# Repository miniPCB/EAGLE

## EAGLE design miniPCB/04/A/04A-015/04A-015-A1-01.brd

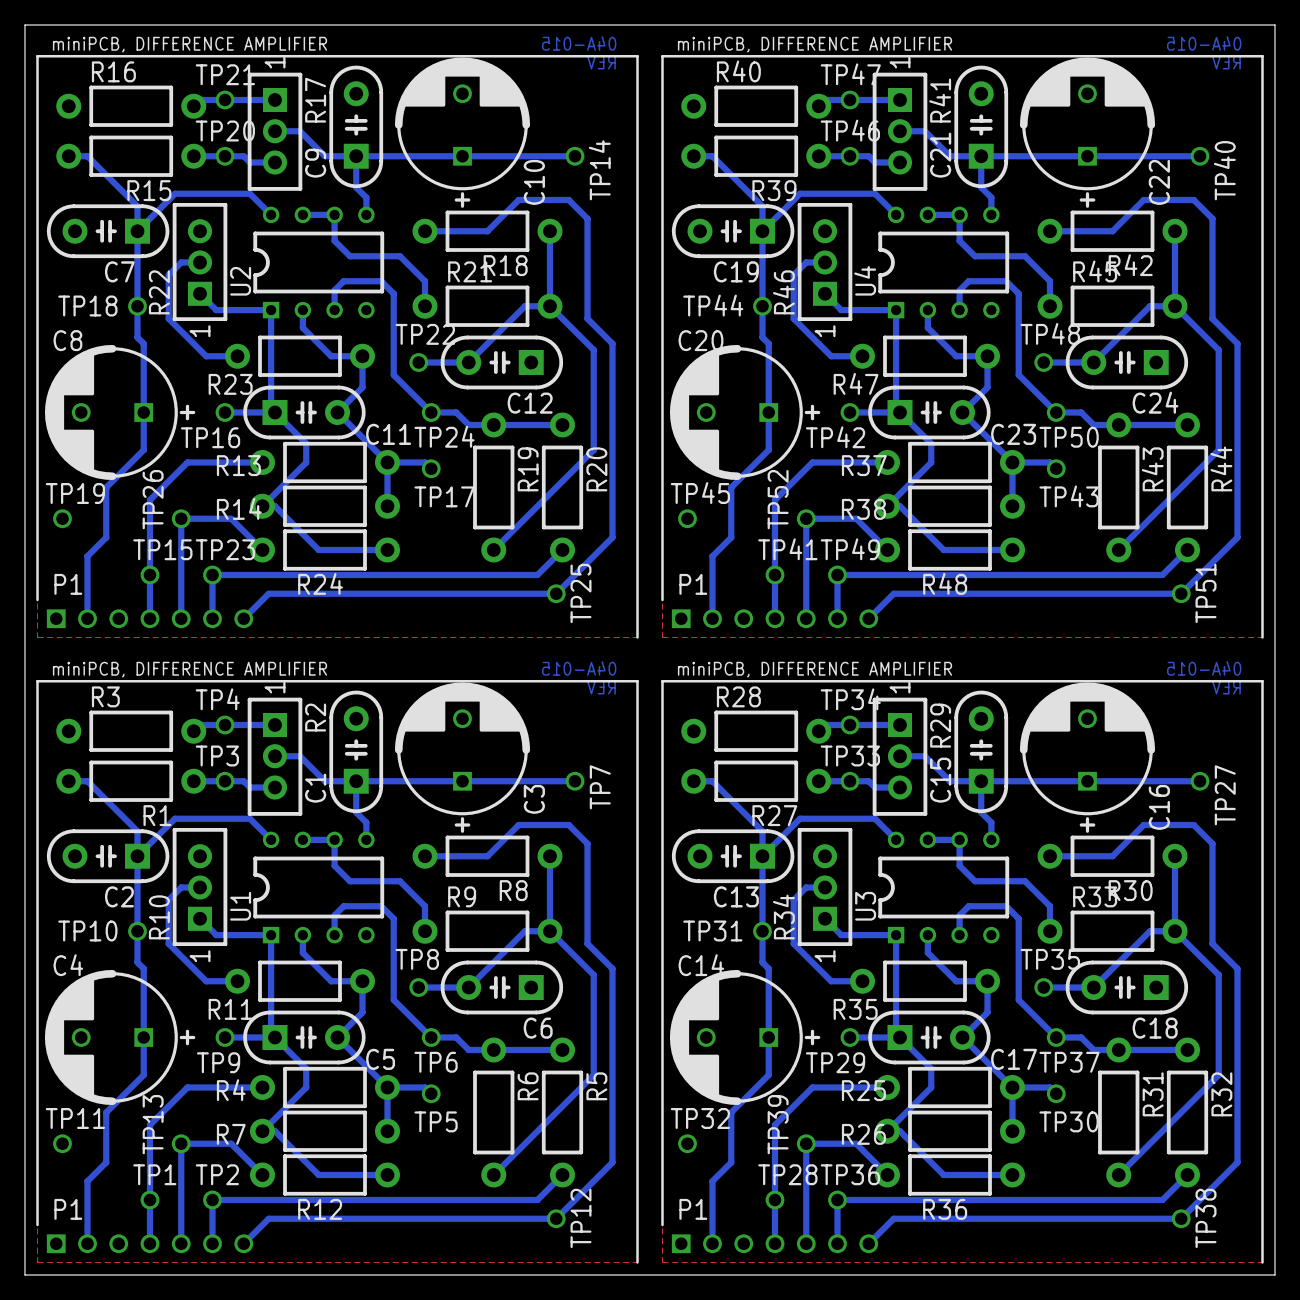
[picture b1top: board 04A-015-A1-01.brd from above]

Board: 2 copper layers, 100.0 x 100.0 mm, 136 parts (0 on the bottom side), 60 nets.

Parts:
C1, C2, C5, C6, C7, C9, C11, C12, C13, C15, C17, C18, C19, C21, C23, C24: C050-024X044
C3, C4, C8, C10, C14, C16, C20, C22: C5MM
P1, P2, P3, P4: PINS_1X7
R1, R3, R4, R5, R6, R7, R8, R9, R11, R12, R13, R14, R15, R16, R18, R19, R20, R21, R23, R24, R25, R26, R27, R28, R30, R31, R32, R33, R35, R36, R37, R38, R39, R40, R42, R43, R44, R45, R47, R48: 0207/10
R2, R10, R17, R22, R29, R34, R41, R46: TRIM_0100
TP1, TP2, TP3, TP4, TP5, TP6, TP7, TP8, TP9, TP10, TP11, TP12, TP13, TP14, TP15, TP16, TP17, TP18, TP19, TP20, TP21, TP22, TP23, TP24, TP25, TP26, TP27, TP28, TP29, TP30, TP31, TP32, TP33, TP34, TP35, TP36, TP37, TP38, TP39, TP40, TP41, TP42, TP43, TP44, TP45, TP46, TP47, TP48, TP49, TP50, TP51, TP52: PINS_1_TESTPOINT_KE5000_NOTEXT
U1, U2, U3, U4: DIL08
U$1, U$2, U$3, U$4: CLASSIC-50; PCB50

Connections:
GND: C1.2, C2.2, C3.-, C4.-, C6.1, P2.1, R3.1, TP11.1, U1.4
GND1: C7.2, C8.-, C9.2, C10.-, C12.1, P1.1, R16.1, TP19.1, U2.4
GND2: C13.2, C14.-, C15.2, C16.-, C18.1, P3.1, R28.1, TP32.1, U3.4
GND3: C19.2, C20.-, C21.2, C22.-, C24.1, P4.1, R40.1, TP45.1, U4.4
IN+: P2.4, R4.2, TP1.1
IN+1: P1.4, R13.2, TP15.1
IN+2: P3.4, R25.2, TP28.1
IN+3: P4.4, R37.2, TP41.1
IN-: P2.6, R5.2, TP2.1
IN-1: P1.6, R20.2, TP23.1
IN-2: P3.6, R32.2, TP36.1
IN-3: P4.6, R44.2, TP49.1
unnamed: R22.2, R23.2
unnamed: R34.2, R35.2
unnamed: R46.2, R47.2
unnamed: R10.2, R11.2
OUT: C5.1, R7.2, R10.1, R12.1, TP9.1, U1.1
OUT1: C11.1, R14.2, R22.1, R24.1, TP16.1, U2.1
OUT2: C17.1, R26.2, R34.1, R36.1, TP29.1, U3.1
OUT3: C23.1, R38.2, R46.1, R48.1, TP42.1, U4.1
OUTPUT: P2.5, R12.2, TP13.1
OUTPUT1: P1.5, R24.2, TP26.1
OUTPUT2: P3.5, R36.2, TP39.1
OUTPUT3: P4.5, R48.2, TP52.1
OUTREF: P2.7, R8.2, TP12.1
OUTREF1: P1.7, R18.2, TP25.1
OUTREF2: P3.7, R30.2, TP38.1
OUTREF3: P4.7, R42.2, TP51.1
P1.1: R2.1, R3.2, TP4.1
P1.2: R15.1, R17.3, TP20.1
P1.3: R1.1, R2.3, TP3.1
P1.4: R16.2, R17.1, TP21.1
P1.5: R27.1, R29.3, TP33.1
P1.6: R28.2, R29.1, TP34.1
P1.7: R39.1, R41.3, TP46.1
P1.8: R40.2, R41.1, TP47.1
REF: C1.1, C3.+, R2.2, TP7.1, U1.5
REF1: C9.1, C10.+, R17.2, TP14.1, U2.5
REF2: C15.1, C16.+, R29.2, TP27.1, U3.5
REF3: C21.1, C22.+, R41.2, TP40.1, U4.5
V+: C2.1, C4.+, P2.2, R1.2, TP10.1, U1.8
V+1: C7.1, C8.+, P1.2, R15.2, TP18.1, U2.8
V+2: C13.1, C14.+, P3.2, R27.2, TP31.1, U3.8
V+3: C19.1, C20.+, P4.2, R39.2, TP44.1, U4.8
VFB: C5.2, R4.1, R7.1, R11.1, TP5.1, U1.2
VFB1: C11.2, R13.1, R14.1, R23.1, TP17.1, U2.2
VFB2: C17.2, R25.1, R26.1, R35.1, TP30.1, U3.2
VFB3: C23.2, R37.1, R38.1, R47.1, TP43.1, U4.2
VFBREF: R9.1, U1.6, U1.7
VFBREF1: R21.1, U2.6, U2.7
VFBREF2: R33.1, U3.6, U3.7
VFBREF3: R45.1, U4.6, U4.7
VPOS: R5.1, R6.1, TP6.1, U1.3
VPOS1: R19.1, R20.1, TP24.1, U2.3
VPOS2: R31.1, R32.1, TP37.1, U3.3
VPOS3: R43.1, R44.1, TP50.1, U4.3
VREF: C6.2, R6.2, R8.1, R9.2, TP8.1
VREF1: C12.2, R18.1, R19.2, R21.2, TP22.1
VREF2: C18.2, R30.1, R31.2, R33.2, TP35.1
VREF3: C24.2, R42.1, R43.2, R45.2, TP48.1

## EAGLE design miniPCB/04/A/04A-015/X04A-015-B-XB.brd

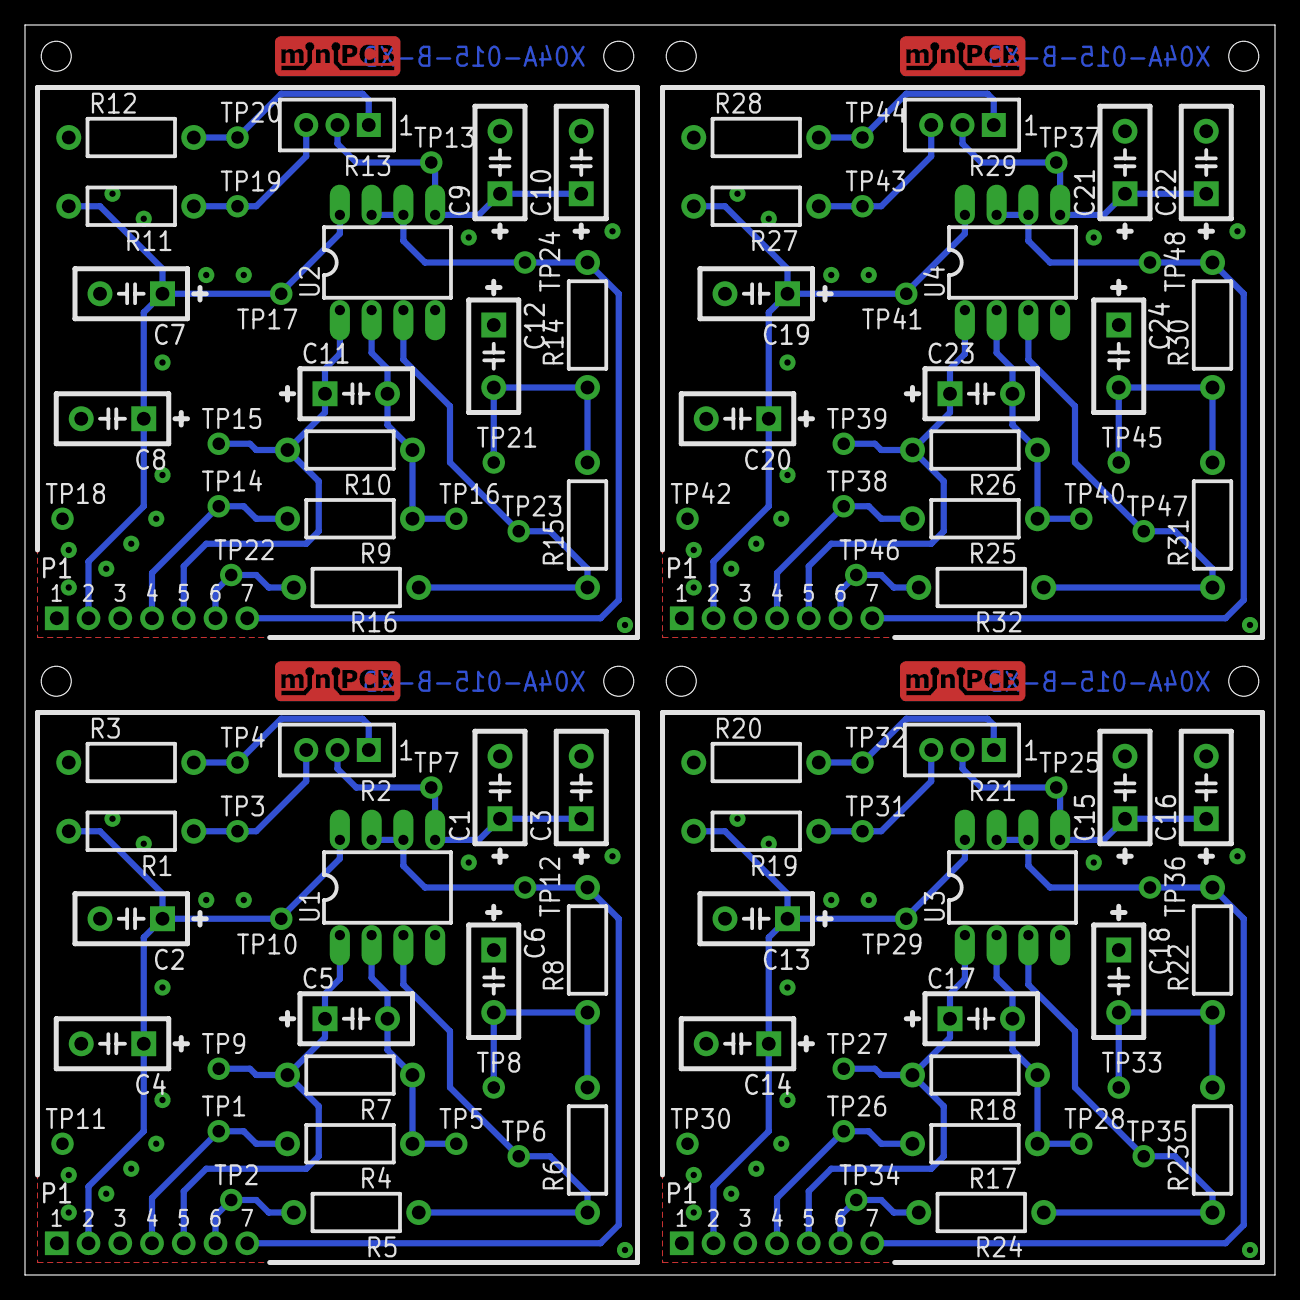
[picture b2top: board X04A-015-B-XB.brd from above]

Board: 2 copper layers, 100.0 x 100.0 mm, 113 parts (0 on the bottom side), 48 nets.

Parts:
C1, C2, C3, C4, C5, C6, C7, C8, C9, C10, C11, C12, C13, C14, C15, C16, C17, C18, C19, C20, C21, C22, C23, C24: C050-024X044
E$1: MINIPCB_PANEL_IMAGEFRAME
P1-, P1-1, P1-2, P1-3: MINIPCB_7P_50X50
R1, R3, R4, R5, R6, R7, R8, R9, R10, R11, R12, R14, R15, R16, R17, R18, R19, R20, R22, R23, R24, R25, R26, R27, R28, R30, R31, R32: 0207/10
R2, R13, R21, R29: TRIM_0100
TP1, TP2, TP3, TP4, TP5, TP6, TP7, TP8, TP9, TP10, TP11, TP12, TP13, TP14, TP15, TP16, TP17, TP18, TP19, TP20, TP21, TP22, TP23, TP24, TP25, TP26, TP27, TP28, TP29, TP30, TP31, TP32, TP33, TP34, TP35, TP36, TP37, TP38, TP39, TP40, TP41, TP42, TP43, TP44, TP45, TP46, TP47, TP48: PINS_1_TESTPOINT_KE5000_NOTEXT
U1, U2, U3, U4: DIL08

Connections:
GND: C1.2, C2.2, C3.2, C4.2, C6.1, P1-.1, R3.1, TP11.1, U1.4
GND1: C7.2, C8.2, C9.2, C10.2, C12.1, P1-1.1, R12.1, TP18.1, U2.4
GND2: C13.2, C14.2, C15.2, C16.2, C18.1, P1-2.1, R20.1, TP30.1, U3.4
GND3: C19.2, C20.2, C21.2, C22.2, C24.1, P1-3.1, R28.1, TP42.1, U4.4
IN: P1-.4, R4.2, TP1.1
IN1: P1-1.4, R9.2, TP14.1
IN2: P1-2.4, R17.2, TP26.1
IN3: P1-3.4, R25.2, TP38.1
unnamed: C1.1, C3.1, R2.2, TP7.1, U1.5
unnamed: C6.2, R6.2, R8.1, TP8.1
unnamed: R5.1, R6.1, TP6.1, U1.3
unnamed: P1-.6, R5.2, TP2.1
unnamed: C9.1, C10.1, R13.2, TP13.1, U2.5
unnamed: C12.2, R14.1, R15.2, TP21.1
unnamed: R15.1, R16.1, TP23.1, U2.3
unnamed: P1-1.6, R16.2, TP22.1
unnamed: C15.1, C16.1, R21.2, TP25.1, U3.5
unnamed: C18.2, R22.1, R23.2, TP33.1
unnamed: R23.1, R24.1, TP35.1, U3.3
unnamed: P1-2.6, R24.2, TP34.1
unnamed: C21.1, C22.1, R29.2, TP37.1, U4.5
unnamed: C24.2, R30.1, R31.2, TP45.1
unnamed: R31.1, R32.1, TP47.1, U4.3
unnamed: P1-3.6, R32.2, TP46.1
OUT: C5.1, P1-.5, R7.2, TP9.1, U1.1
OUT1: C11.1, P1-1.5, R10.2, TP15.1, U2.1
OUT2: C17.1, P1-2.5, R18.2, TP27.1, U3.1
OUT3: C23.1, P1-3.5, R26.2, TP39.1, U4.1
P1.1: R2.1, R3.2, TP4.1
P1.2: R11.1, R13.3, TP19.1
P1.3: R1.1, R2.3, TP3.1
P1.4: R12.2, R13.1, TP20.1
P1.5: R19.1, R21.3, TP31.1
P1.6: R20.2, R21.1, TP32.1
P1.7: R27.1, R29.3, TP43.1
P1.8: R28.2, R29.1, TP44.1
V+: C2.1, C4.1, P1-.2, R1.2, TP10.1, U1.8
V+1: C7.1, C8.1, P1-1.2, R11.2, TP17.1, U2.8
V+2: C13.1, C14.1, P1-2.2, R19.2, TP29.1, U3.8
V+3: C19.1, C20.1, P1-3.2, R27.2, TP41.1, U4.8
VFB: C5.2, R4.1, R7.1, TP5.1, U1.2
VFB1: C11.2, R9.1, R10.1, TP16.1, U2.2
VFB2: C17.2, R17.1, R18.1, TP28.1, U3.2
VFB3: C23.2, R25.1, R26.1, TP40.1, U4.2
VREF: P1-.7, R8.2, TP12.1, U1.6, U1.7
VREF1: P1-1.7, R14.2, TP24.1, U2.6, U2.7
VREF2: P1-2.7, R22.2, TP36.1, U3.6, U3.7
VREF3: P1-3.7, R30.2, TP48.1, U4.6, U4.7

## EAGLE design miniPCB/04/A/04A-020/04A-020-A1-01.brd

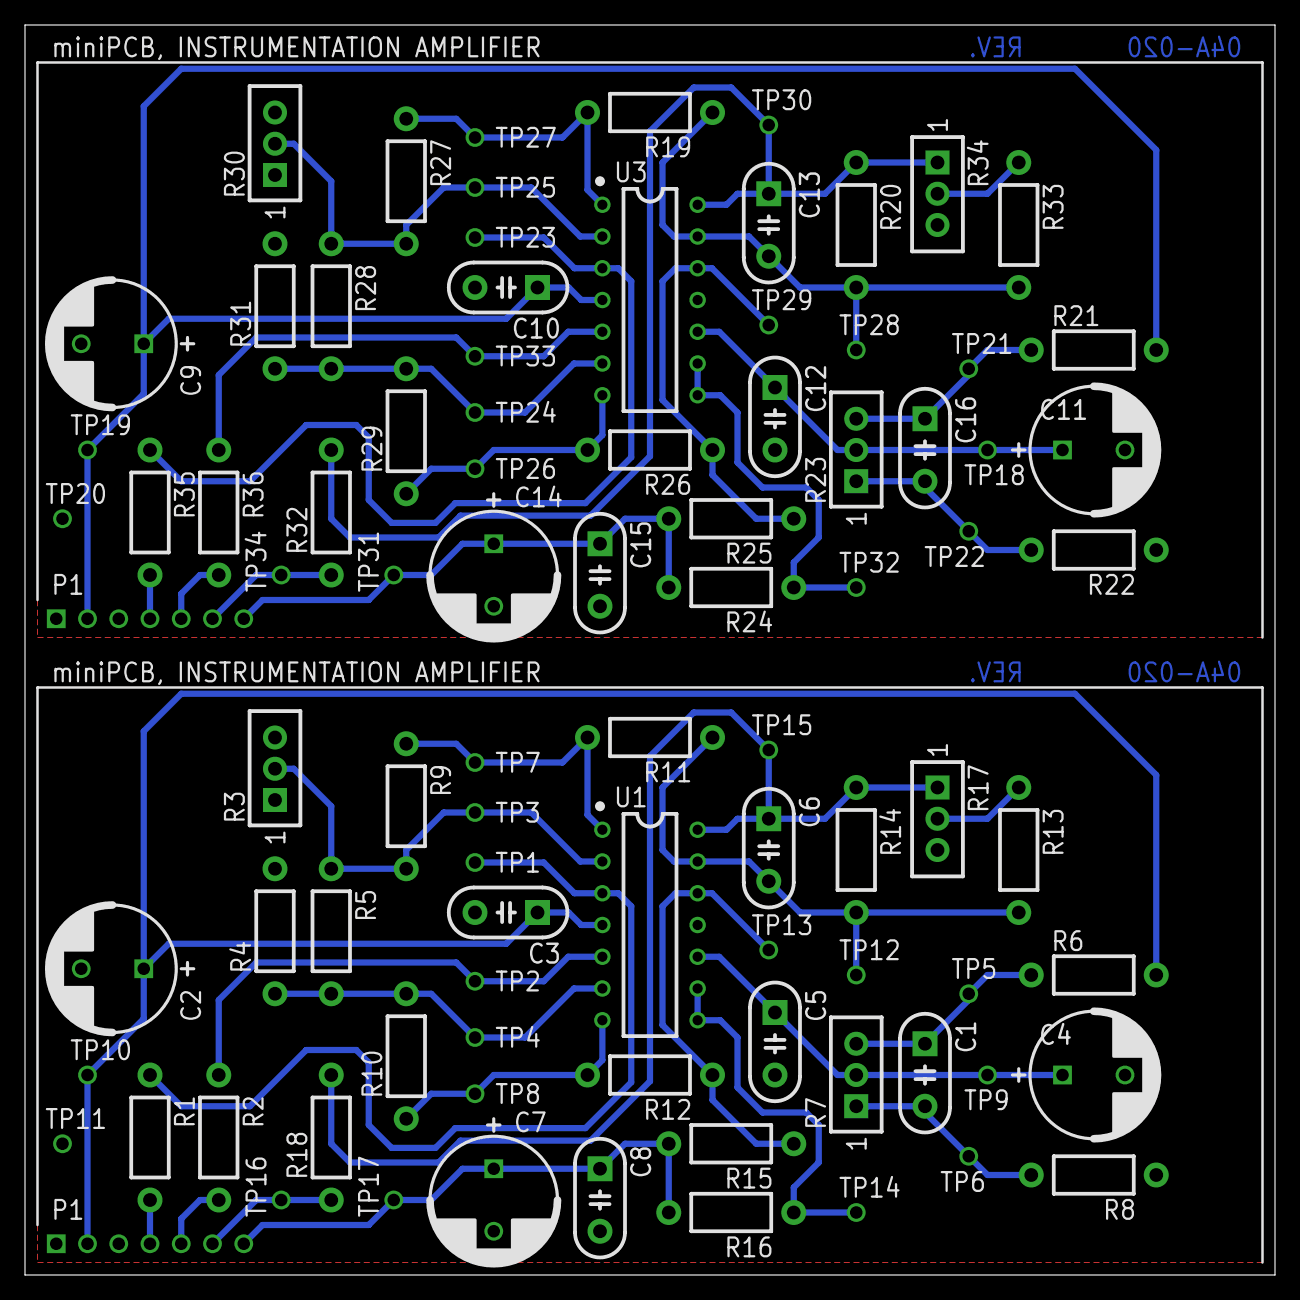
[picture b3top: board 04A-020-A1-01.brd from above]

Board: 2 copper layers, 100.0 x 100.0 mm, 92 parts (0 on the bottom side), 42 nets.

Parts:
C1, C3, C5, C6, C8, C10, C12, C13, C15, C16: C050-024X044
C2, C4, C7, C9, C11, C14: C5MM
P1, P2: PINS_1X7
R1, R2, R4, R5, R6, R8, R9, R10, R11, R12, R13, R14, R15, R16, R18, R19, R20, R21, R22, R24, R25, R26, R27, R28, R29, R31, R32, R33, R35, R36: 0207/10
R3, R7, R17, R23, R30, R34: TRIM_0100
TP1, TP2, TP3, TP4, TP5, TP6, TP7, TP8, TP9, TP10, TP11, TP12, TP13, TP14, TP15, TP16, TP17, TP18, TP19, TP20, TP21, TP22, TP23, TP24, TP25, TP26, TP27, TP28, TP29, TP30, TP31, TP32, TP33, TP34: PINS_1_TESTPOINT_KE5000_NOTEXT
U1, U3: DIL14
U2, U4: CLASSIC-50X100; PCB50X100

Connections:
BIAS: C4.+, C5.1, R7.2, TP9.1, U1.10
BIAS1: C11.+, C12.1, R23.2, TP18.1, U3.10
GND: C2.-, C3.2, C4.-, C5.2, C7.-, C8.2, P1.1, R8.1, TP11.1, U1.11
GND1: C9.-, C10.2, C11.-, C12.2, C14.-, C15.2, P2.1, R22.1, TP20.1, U3.11
unnamed: R12.1, R15.1, TP13.1, U1.12
unnamed: C7.+, C8.1, P1.7, R15.2, R16.2, TP17.1
unnamed: R2.1, TP2.1, U1.5
unnamed: R1.1, TP1.1, U1.3
unnamed: R3.2, R5.1, R9.2, TP3.1, U1.2
unnamed: R4.1, R5.2, R10.2, TP4.1, U1.6
unnamed: R9.1, R11.2, TP7.1, U1.1
unnamed: R10.1, R12.2, TP8.1, U1.7
unnamed: R16.1, TP14.1, U1.8, U1.9
unnamed: R3.1, R4.2
unnamed: P1.6, R18.1, TP16.1
unnamed: R13.1, R17.2
unnamed: P1.4, R1.2
unnamed: P1.5, R2.2
unnamed: R25.1, R26.1, TP29.1, U3.12
unnamed: C14.+, C15.1, P2.7, R24.2, R25.2, TP31.1
unnamed: R36.1, TP33.1, U3.5
unnamed: R35.1, TP23.1, U3.3
unnamed: R27.2, R28.1, R30.2, TP25.1, U3.2
unnamed: R28.2, R29.2, R31.1, TP24.1, U3.6
unnamed: R19.2, R27.1, TP27.1, U3.1
unnamed: R26.2, R29.1, TP26.1, U3.7
unnamed: R24.1, TP32.1, U3.8, U3.9
unnamed: R30.1, R31.2
unnamed: P2.6, R32.1, TP34.1
unnamed: R33.1, R34.2
unnamed: P2.4, R35.2
unnamed: P2.5, R36.2
OUT: C6.1, R14.1, R17.1, R18.2, TP15.1, U1.14
OUT1: C13.1, R20.1, R32.2, R34.1, TP30.1, U3.14
POT.1: C1.2, R7.1, R8.2, TP6.1
POT.2: C16.1, R21.1, R23.3, TP21.1
POT.3: C1.1, R6.1, R7.3, TP5.1
POT.4: C16.2, R22.2, R23.1, TP22.1
V+: C2.+, C3.1, P1.2, R6.2, TP10.1, U1.4
V+1: C9.+, C10.1, P2.2, R21.2, TP19.1, U3.4
VFB: C6.2, R11.1, R13.2, R14.2, TP12.1, U1.13
VFB1: C13.2, R19.1, R20.2, R33.2, TP28.1, U3.13

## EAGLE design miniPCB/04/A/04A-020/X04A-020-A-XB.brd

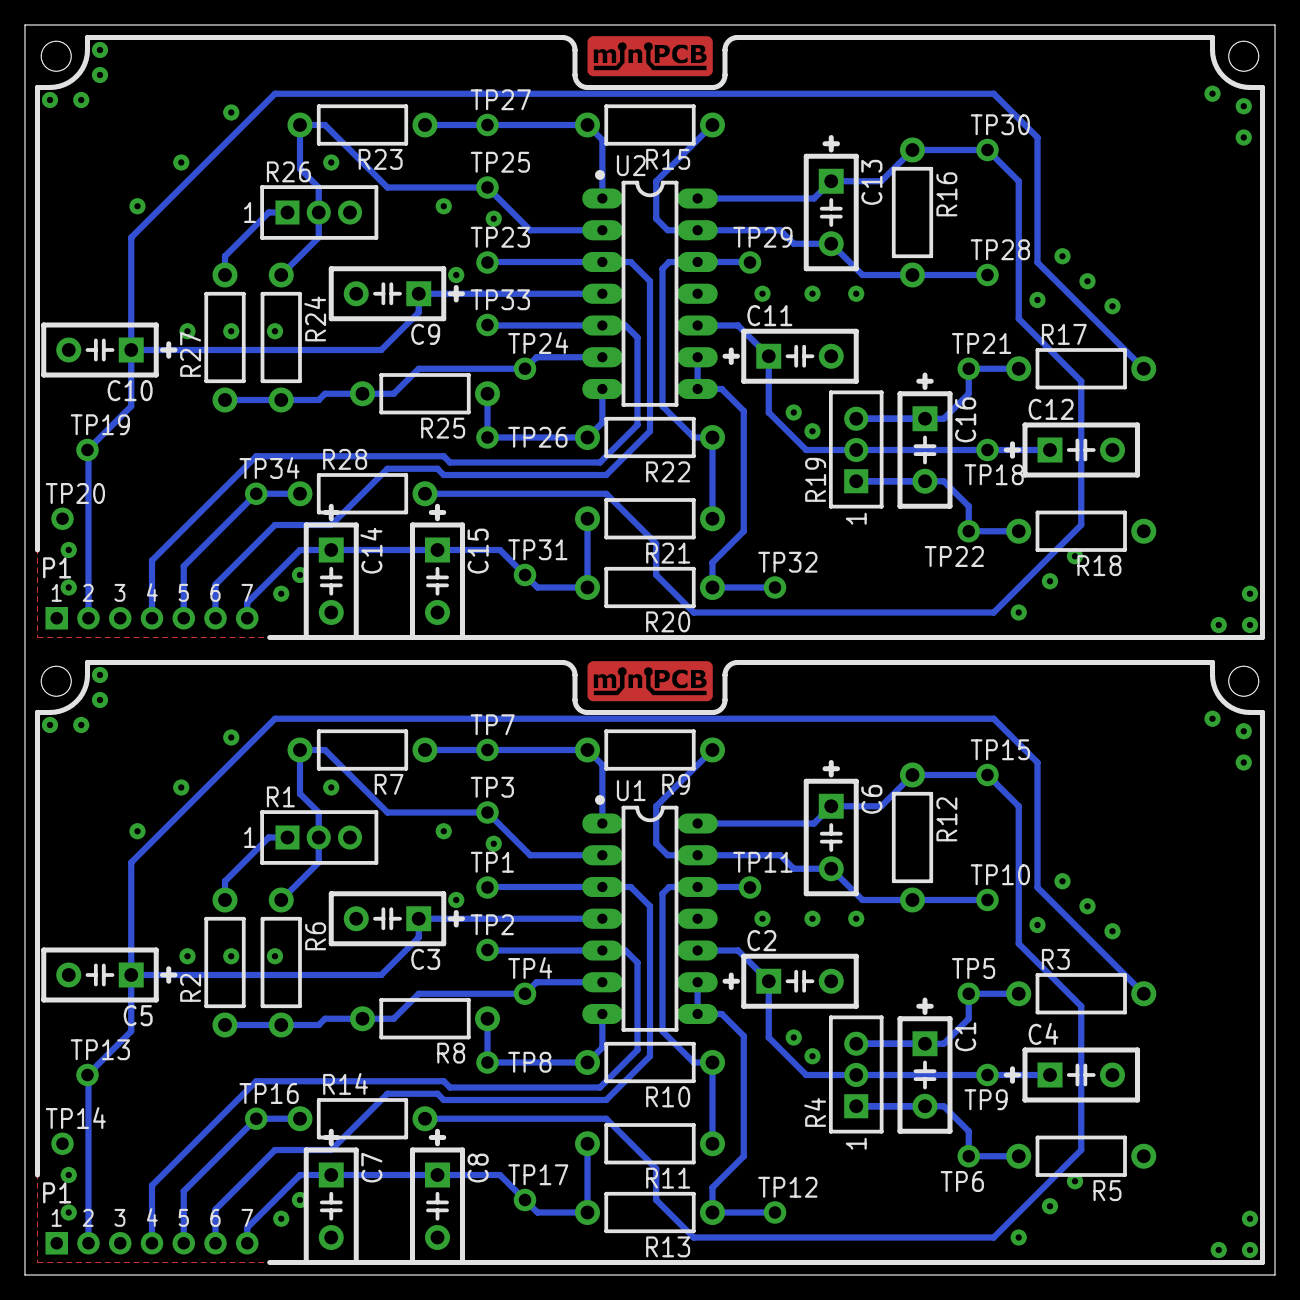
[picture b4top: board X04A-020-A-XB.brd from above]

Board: 2 copper layers, 100.0 x 100.0 mm, 83 parts (0 on the bottom side), 36 nets.

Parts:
C1, C2, C3, C4, C5, C6, C7, C8, C9, C10, C11, C12, C13, C14, C15, C16: C050-024X044
E$1: MINIPCB_PANEL_IMAGEFRAME
P1-, P1-1: MINIPCB_7P_50X100
R1, R4, R19, R26: TRIM_0100
R2, R3, R5, R6, R7, R8, R9, R10, R11, R12, R13, R14, R15, R16, R17, R18, R20, R21, R22, R23, R24, R25, R27, R28: 0207/10
TP1, TP2, TP3, TP4, TP5, TP6, TP7, TP8, TP9, TP10, TP11, TP12, TP13, TP14, TP15, TP16, TP17, TP18, TP19, TP20, TP21, TP22, TP23, TP24, TP25, TP26, TP27, TP28, TP29, TP30, TP31, TP32, TP33, TP34: PINS_1_TESTPOINT_KE5000_NOTEXT
U1, U2: OPAMP_QUADTHD; DIL14

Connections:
BIAS: C2.1, C4.1, R4.2, TP9.1, U1.10
BIAS1: C11.1, C12.1, R19.2, TP18.1, U2.10
GND: C2.2, C3.2, C4.2, C5.2, C7.2, C8.2, P1-.1, R5.1, TP14.1, U1.11
GND1: C9.2, C10.2, C11.2, C12.2, C14.2, C15.2, P1-1.1, R18.1, TP20.1, U2.11
unnamed: R10.1, R11.1, TP11.1, U1.12
unnamed: C7.1, C8.1, P1-.7, R11.2, R13.2, TP17.1
unnamed: P1-.4, TP2.1, U1.5
unnamed: P1-.6, TP1.1, U1.3
unnamed: R1.2, R6.1, R7.2, TP3.1, U1.2
unnamed: R2.1, R6.2, R8.2, TP4.1, U1.6
unnamed: R7.1, R9.2, TP7.1, U1.1
unnamed: R8.1, R10.2, TP8.1, U1.7
unnamed: R13.1, TP12.1, U1.8, U1.9
unnamed: R1.1, R2.2
unnamed: P1-.5, R14.1, TP16.1
unnamed: R21.1, R22.1, TP29.1, U2.12
unnamed: C14.1, C15.1, P1-1.7, R20.2, R21.2, TP31.1
unnamed: P1-1.4, TP33.1, U2.5
unnamed: P1-1.6, TP23.1, U2.3
unnamed: R23.2, R24.1, R26.2, TP25.1, U2.2
unnamed: R24.2, R25.2, R27.1, TP24.1, U2.6
unnamed: R15.2, R23.1, TP27.1, U2.1
unnamed: R22.2, R25.1, TP26.1, U2.7
unnamed: R20.1, TP32.1, U2.8, U2.9
unnamed: R26.1, R27.2
unnamed: P1-1.5, R28.1, TP34.1
OUT: C6.1, R12.1, R14.2, TP15.1, U1.14
OUT1: C13.1, R16.1, R28.2, TP30.1, U2.14
POT.1: C1.2, R4.1, R5.2, TP6.1
POT.2: C16.1, R17.1, R19.3, TP21.1
POT.3: C1.1, R3.1, R4.3, TP5.1
POT.4: C16.2, R18.2, R19.1, TP22.1
V+: C3.1, C5.1, P1-.2, R3.2, TP13.1, U1.4
V+1: C9.1, C10.1, P1-1.2, R17.2, TP19.1, U2.4
VFB: C6.2, R9.1, R12.2, TP10.1, U1.13
VFB1: C13.2, R15.1, R16.2, TP28.1, U2.13

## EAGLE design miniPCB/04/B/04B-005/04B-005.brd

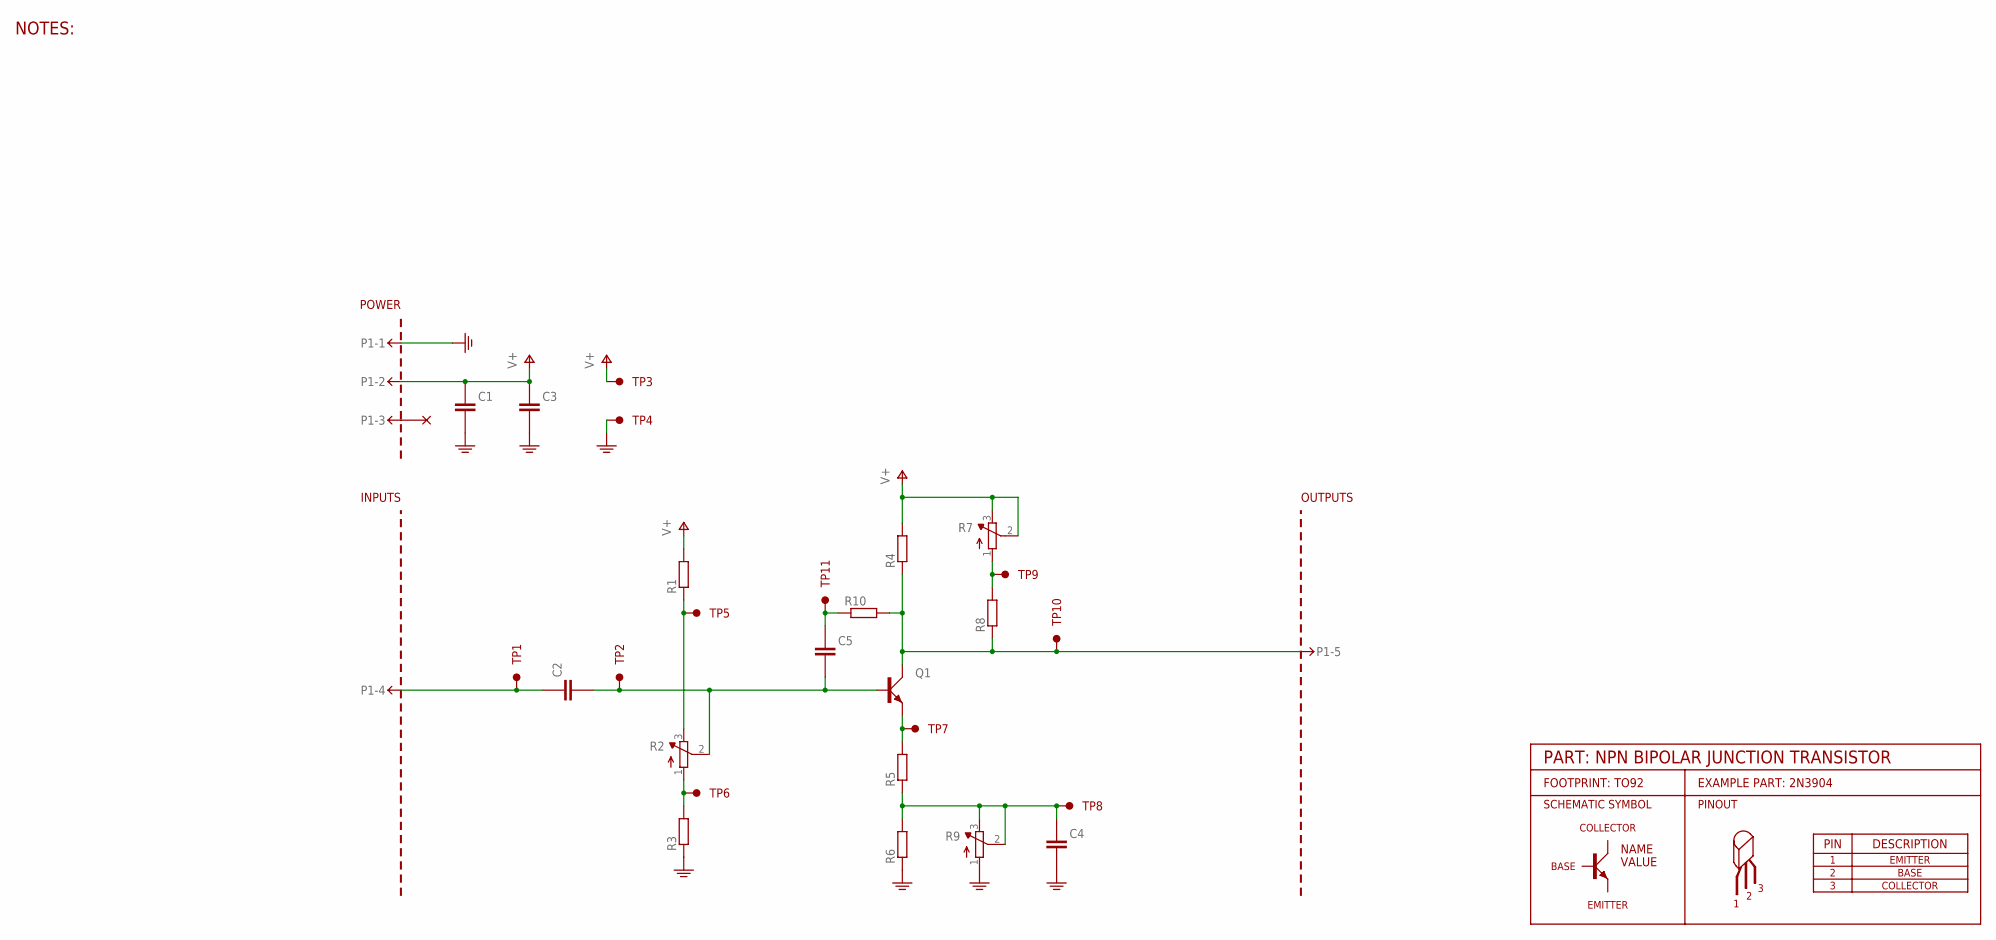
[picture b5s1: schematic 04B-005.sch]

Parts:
C1, C2, C3, C4, C5: CAPACITORTHD; C050-024X044
P1-: MINIPCB_5P50X50; MINIPCB_5P_50X50MM; PART_NUMBER X04B-005-B
Q1: BJT_NPNEBC; TO92-EBC-OVAL
R1, R3, R4, R5, R6, R8, R10: RESISTOR10MM; 0207/10
R2, R7, R9: TRIMPOT0.100THD; TRIM_0100
TP1, TP2, TP3, TP4, TP5, TP6, TP7, TP8, TP9, TP10, TP11: TESTPOINTKE5000-SMTEXT; PINS_1_TESTPOINT_KE5000_NOTEXT

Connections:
GND: C1.2 (-), C3.2 (-), C4.2 (-), P1-.1, R3.1, R6.1, R9.1 (A), TP4.1
unnamed: R7.1 (A), R8.2, TP9.1
unnamed: R1.1, R2.3 (E), TP5.1
unnamed: R2.1 (A), R3.2, TP6.1
unnamed: C4.1 (+), R5.1, R6.2, R9.2 (S), R9.3 (E), TP8.1
unnamed: C2.2 (-), C5.2 (-), Q1.B, R2.2 (S), TP2.1
unnamed: Q1.E, R5.2, TP7.1
unnamed: C5.1 (+), R10.1, TP11.1
unnamed: P1-.5, Q1.C, R4.1, R8.1, R10.2, TP10.1
unnamed: C2.1 (+), P1-.4, TP1.1
V+: C1.1 (+), C3.1 (+), P1-.2, R1.2, R4.2, R7.2 (S), R7.3 (E), TP3.1

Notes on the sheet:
NOTES:

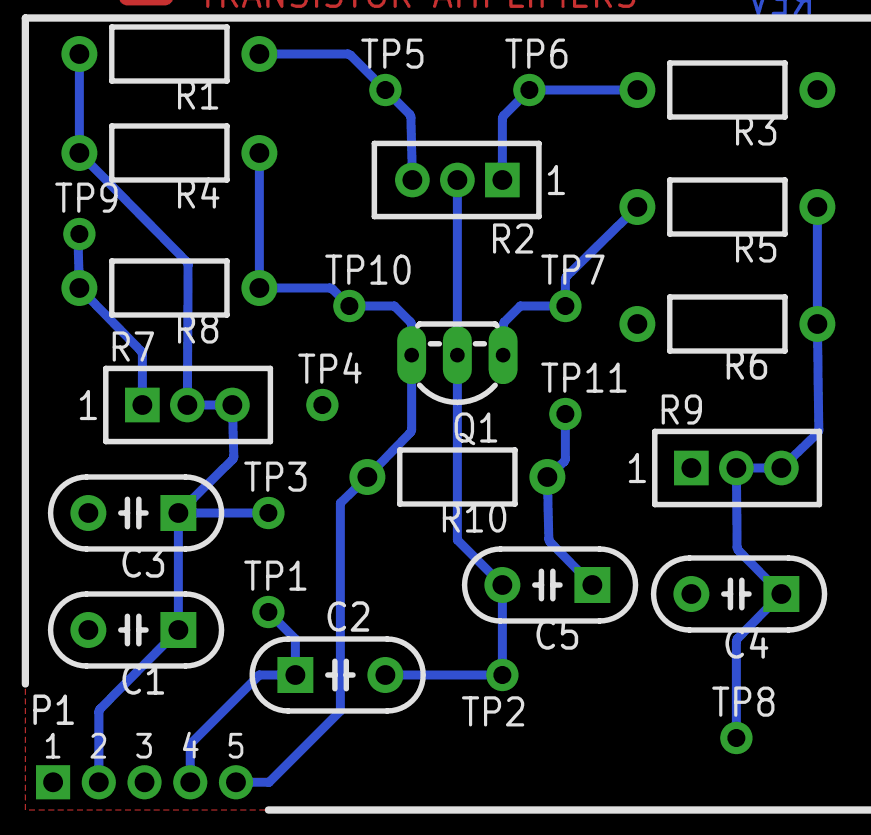
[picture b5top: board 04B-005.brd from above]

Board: 2 copper layers, 28 parts (0 on the bottom side), 11 nets.
